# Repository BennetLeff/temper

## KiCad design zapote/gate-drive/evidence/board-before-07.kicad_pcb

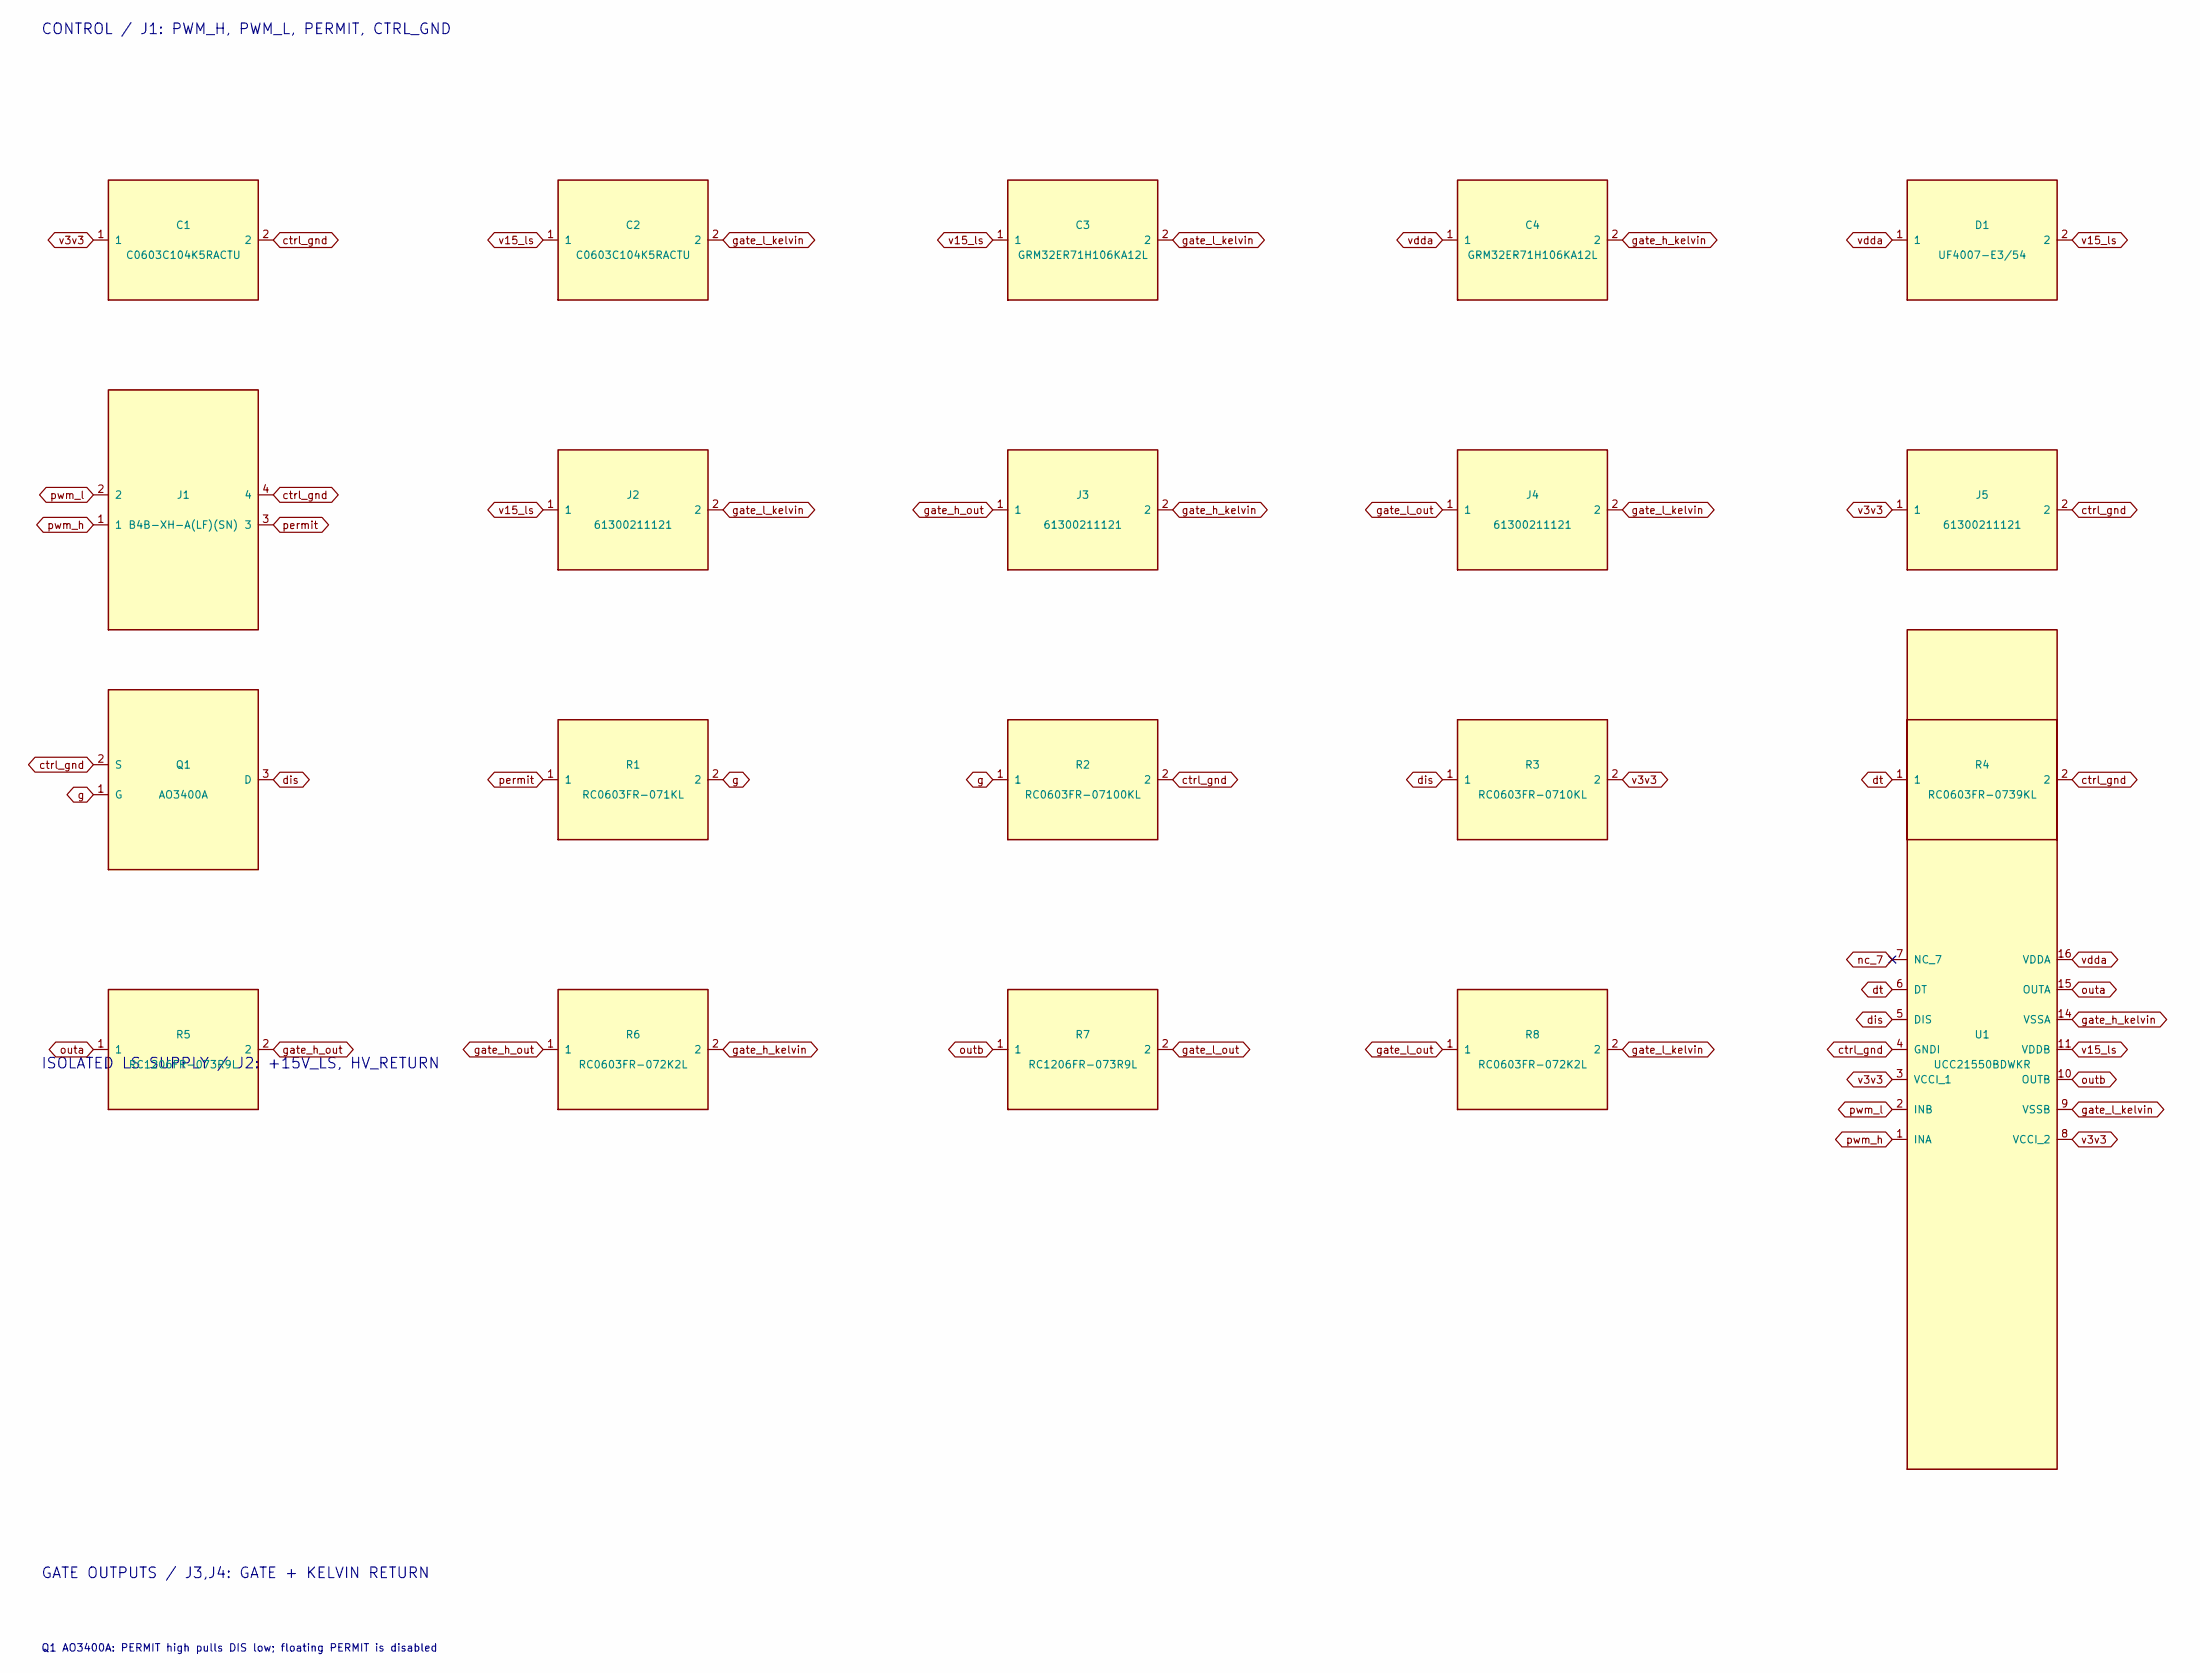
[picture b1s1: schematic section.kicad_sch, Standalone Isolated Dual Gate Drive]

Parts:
C1, C2: C0603C104K5RACTU; C_0603_1608Metric
C3, C4: GRM32ER71H106KA12L; C_1210_3225Metric
D1: UF4007-E3/54; D_DO-41_SOD81_P10.16mm_Horizontal
J1: B4B-XH-A(LF)(SN); JST_XH_B4B-XH-A_1x04_P2.50mm_Vertical
J2, J3, J4, J5: 61300211121; PinHeader_1x02_P2.54mm_Vertical
Q1: AO3400A; SOT-23
R1: RC0603FR-071KL; R_0603_1608Metric
R2: RC0603FR-07100KL; R_0603_1608Metric
R3: RC0603FR-0710KL; R_0603_1608Metric
R4: RC0603FR-0739KL; R_0603_1608Metric
R5, R7: RC1206FR-073R9L; R_1206_3216Metric
R6, R8: RC0603FR-072K2L; R_0603_1608Metric
U1: UCC21550BDWKR; SOIC16W_Isolated

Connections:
ctrl_gnd: C1.2, J1.4, J5.2, Q1.2 (S), R2.2, R4.2, U1.4 (GNDI)
dis: Q1.3 (D), R3.1, U1.5 (DIS)
dt: R4.1, U1.6 (DT)
g: Q1.1 (G), R1.2, R2.1
gate_h_kelvin: C4.2, J3.2, R6.2, U1.14 (VSSA)
gate_h_out: J3.1, R5.2, R6.1
gate_l_kelvin: C2.2, C3.2, J2.2, J4.2, R8.2, U1.9 (VSSB)
gate_l_out: J4.1, R7.2, R8.1
nc_7: U1.7 (NC_7)
outa: R5.1, U1.15 (OUTA)
outb: R7.1, U1.10 (OUTB)
permit: J1.3, R1.1
pwm_h: J1.1, U1.1 (INA)
pwm_l: J1.2, U1.2 (INB)
v3v3: C1.1, J5.1, R3.2, U1.3 (VCCI_1), U1.8 (VCCI_2)
v15_ls: C2.1, C3.1, D1.2, J2.1, U1.11 (VDDB)
vdda: C4.1, D1.1, U1.16 (VDDA)

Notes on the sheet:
CONTROL / J1: PWM_H, PWM_L, PERMIT, CTRL_GND
ISOLATED LS SUPPLY / J2: +15V_LS, HV_RETURN
GATE OUTPUTS / J3,J4: GATE + KELVIN RETURN
Q1 AO3400A: PERMIT high pulls DIS low; floating PERMIT is disabled

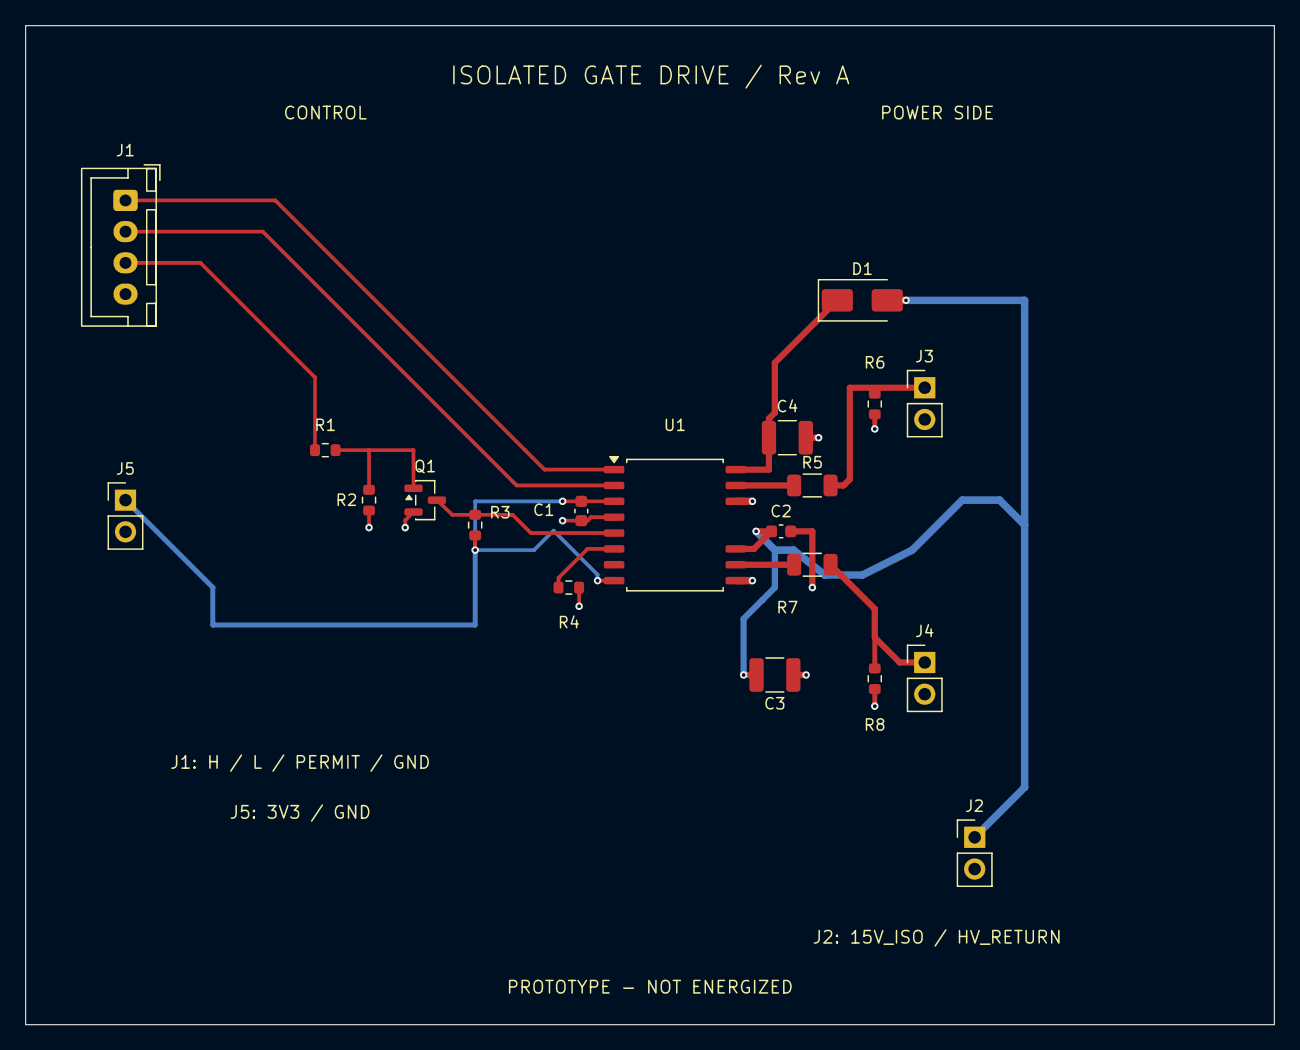
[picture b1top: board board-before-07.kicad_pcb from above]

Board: 2 copper layers, 100.0 x 80.0 mm, 20 parts (0 on the bottom side), 16 nets.

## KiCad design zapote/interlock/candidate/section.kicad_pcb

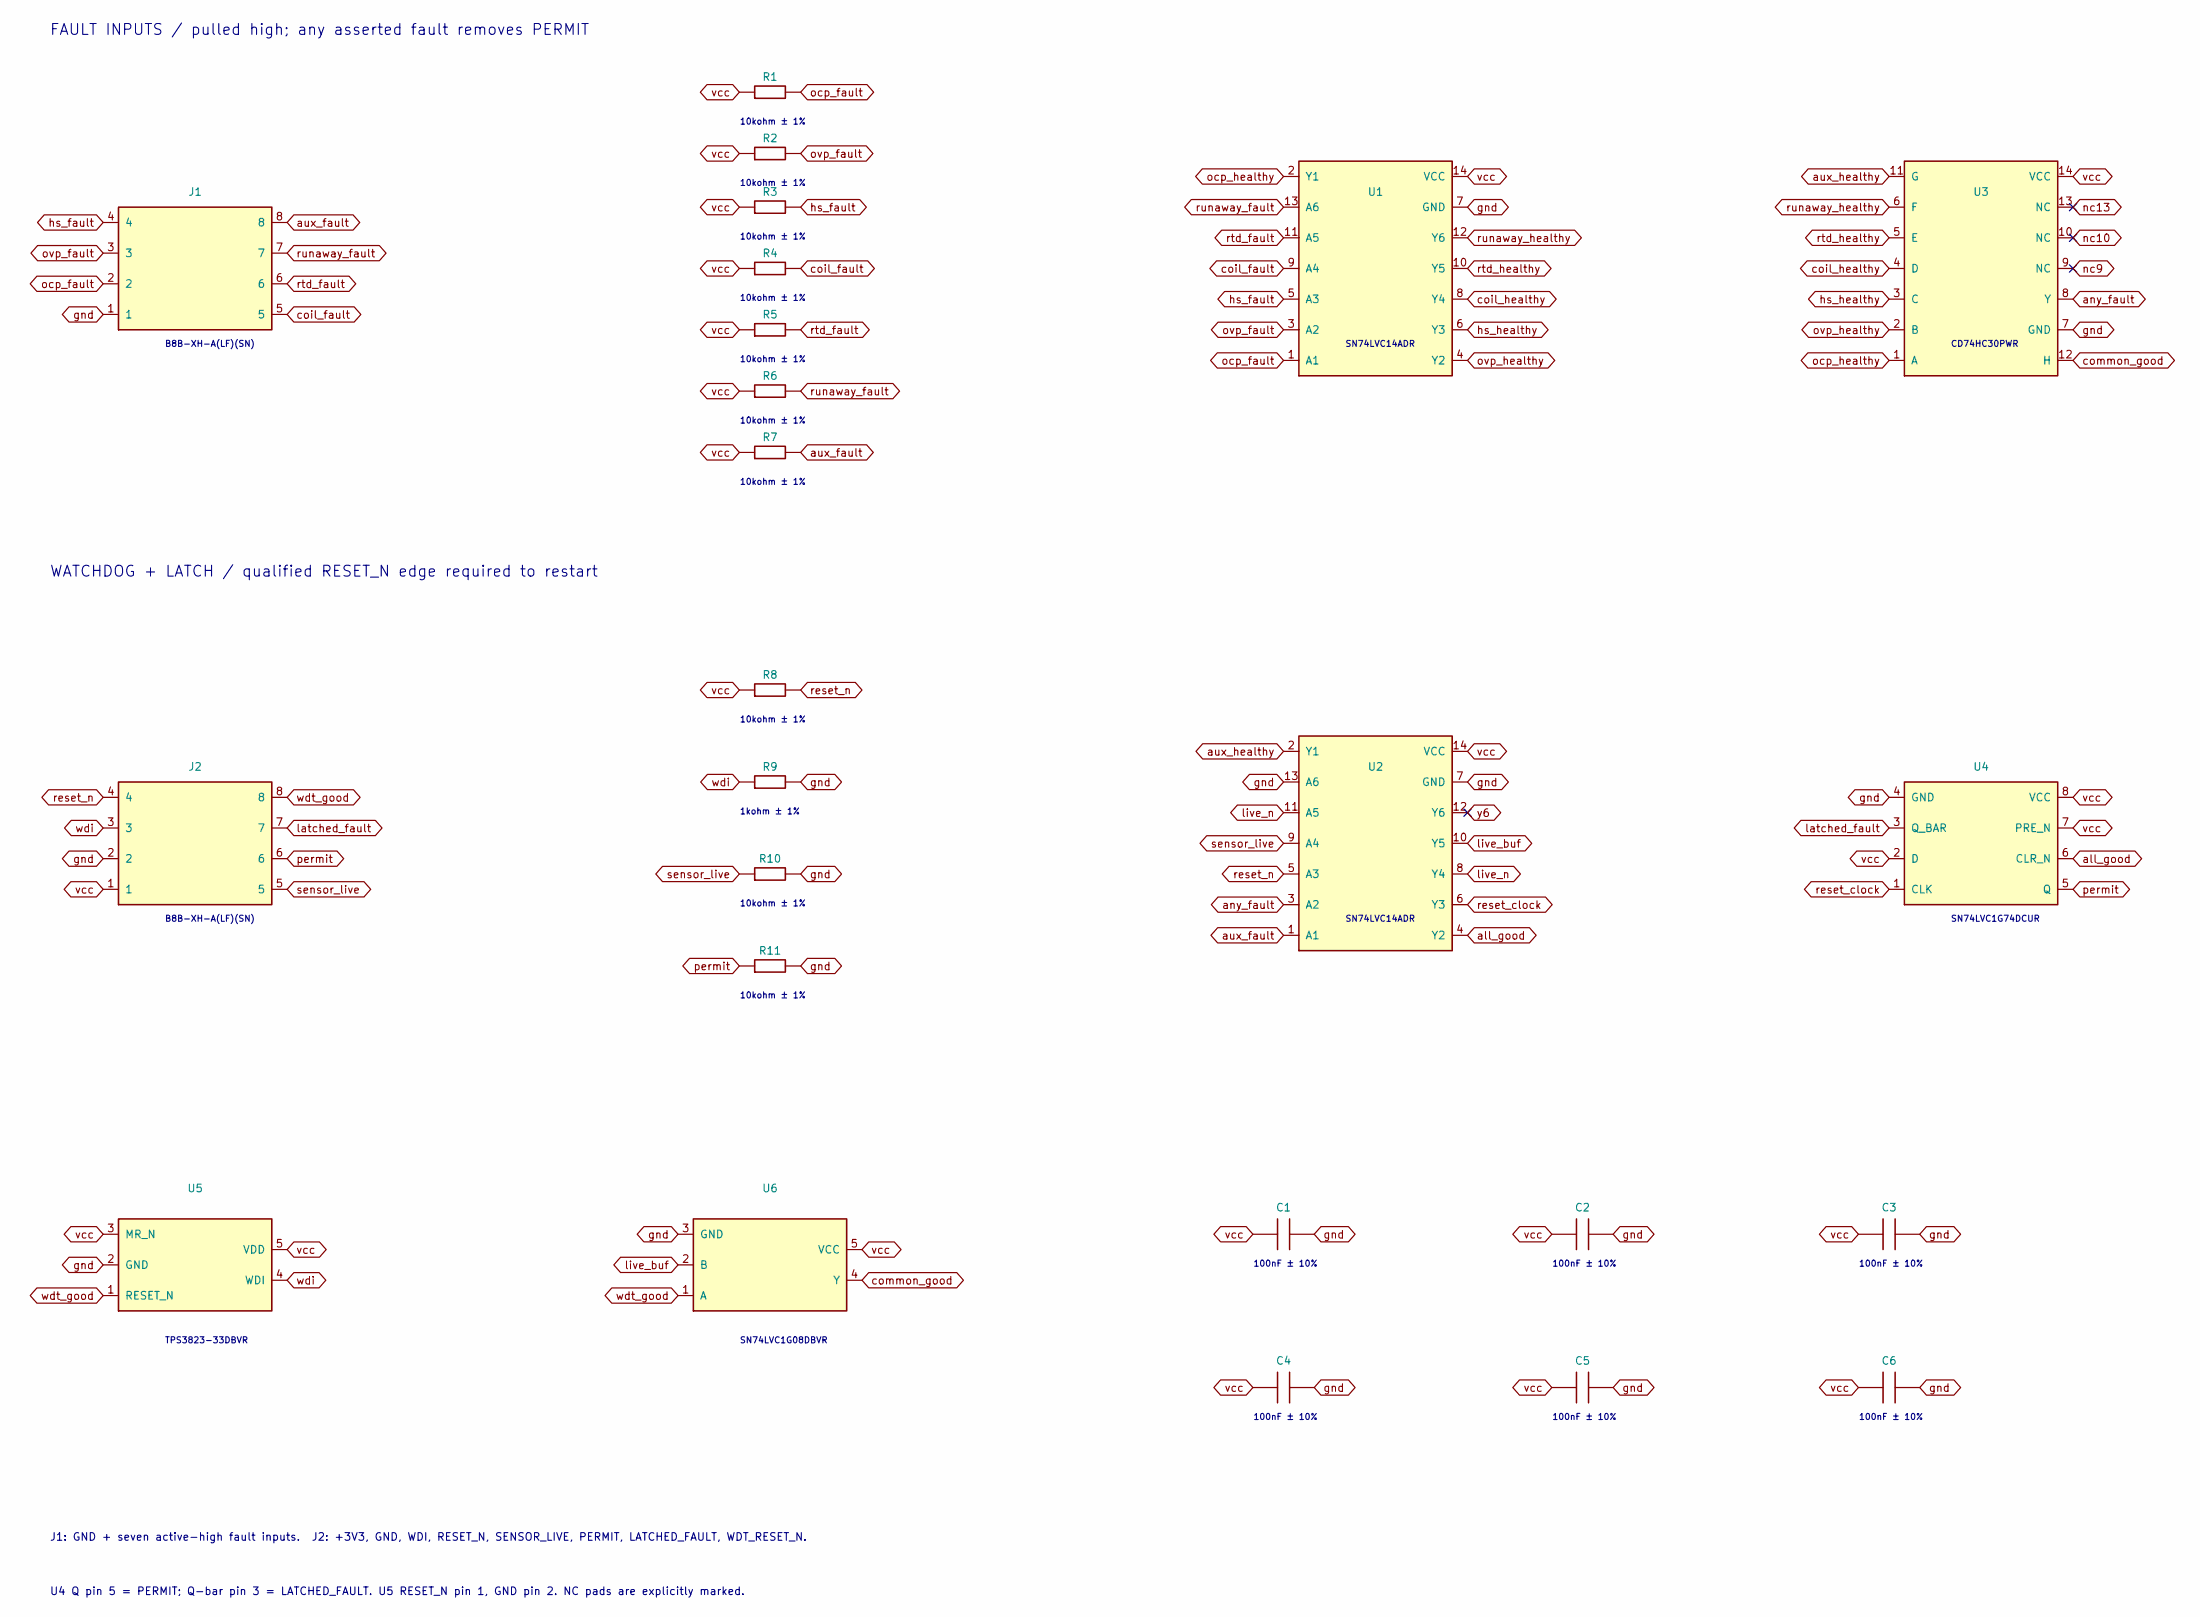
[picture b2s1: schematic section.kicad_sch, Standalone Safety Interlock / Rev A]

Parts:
C1, C2, C3, C4, C5, C6: C0603C104K5RACTU; C_0603_1608Metric
J1, J2: B8B-XH-A(LF)(SN); JST_XH_B8B-XH-A_1x08_P2.50mm_Vertical
R1, R2, R3, R4, R5, R6, R7, R8, R10, R11: RC0603FR-0710KL; R_0603_1608Metric
R9: RC0603FR-071KL; R_0603_1608Metric
U1, U2: SN74LVC14ADR; SOIC-14_3.9x8.7mm_P1.27mm
U3: CD74HC30PWR; TSSOP-14_4.4x5mm_P0.65mm
U4: SN74LVC1G74DCUR; VSSOP-8_2.3x2mm_P0.5mm
U5: TPS3823-33DBVR; SOT-23-5
U6: SN74LVC1G08DBVR; SOT-23-5

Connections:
all_good: U2.4 (Y2), U4.6 (CLR_N)
any_fault: U2.3 (A2), U3.8 (Y)
aux_fault: J1.8, R7.2, U2.1 (A1)
aux_healthy: U2.2 (Y1), U3.11 (G)
coil_fault: J1.5, R4.2, U1.9 (A4)
coil_healthy: U1.8 (Y4), U3.4 (D)
common_good: U3.12 (H), U6.4 (Y)
gnd: C1.2, C2.2, C3.2, C4.2, C5.2, C6.2, J1.1, J2.2, R9.2, R10.2, R11.2, U1.7 (GND), U2.7 (GND), U2.13 (A6), U3.7 (GND), U4.4 (GND), U5.2 (GND), U6.3 (GND)
hs_fault: J1.4, R3.2, U1.5 (A3)
hs_healthy: U1.6 (Y3), U3.3 (C)
latched_fault: J2.7, U4.3 (Q_BAR)
live_buf: U2.10 (Y5), U6.2 (B)
live_n: U2.8 (Y4), U2.11 (A5)
nc9: U3.9 (NC)
nc10: U3.10 (NC)
nc13: U3.13 (NC)
ocp_fault: J1.2, R1.2, U1.1 (A1)
ocp_healthy: U1.2 (Y1), U3.1 (A)
ovp_fault: J1.3, R2.2, U1.3 (A2)
ovp_healthy: U1.4 (Y2), U3.2 (B)
permit: J2.6, R11.1, U4.5 (Q)
reset_clock: U2.6 (Y3), U4.1 (CLK)
reset_n: J2.4, R8.2, U2.5 (A3)
rtd_fault: J1.6, R5.2, U1.11 (A5)
rtd_healthy: U1.10 (Y5), U3.5 (E)
runaway_fault: J1.7, R6.2, U1.13 (A6)
runaway_healthy: U1.12 (Y6), U3.6 (F)
sensor_live: J2.5, R10.1, U2.9 (A4)
vcc: C1.1, C2.1, C3.1, C4.1, C5.1, C6.1, J2.1, R1.1, R2.1, R3.1, R4.1, R5.1, R6.1, R7.1, R8.1, U1.14 (VCC), U2.14 (VCC), U3.14 (VCC), U4.2 (D), U4.7 (PRE_N), U4.8 (VCC), U5.3 (MR_N), U5.5 (VDD), U6.5 (VCC)
wdi: J2.3, R9.1, U5.4 (WDI)
wdt_good: J2.8, U5.1 (RESET_N), U6.1 (A)
y6: U2.12 (Y6)

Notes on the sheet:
FAULT INPUTS / pulled high; any asserted fault removes PERMIT
WATCHDOG + LATCH / qualified RESET_N edge required to restart
J1: GND + seven active-high fault inputs. J2: +3V3, GND, WDI, RESET_N, SENSOR_LIVE, PERMIT, LATCHED_FAULT, WDT_RESET_N.
U4 Q pin 5 = PERMIT; Q-bar pin 3 = LATCHED_FAULT. U5 RESET_N pin 1, GND pin 2. NC pads are explicitly marked.
100nF ± 10%
B8B-XH-A(LF)(SN)
10kohm ± 1%
1kohm ± 1%
SN74LVC14ADR
CD74HC30PWR
SN74LVC1G74DCUR
TPS3823-33DBVR
SN74LVC1G08DBVR

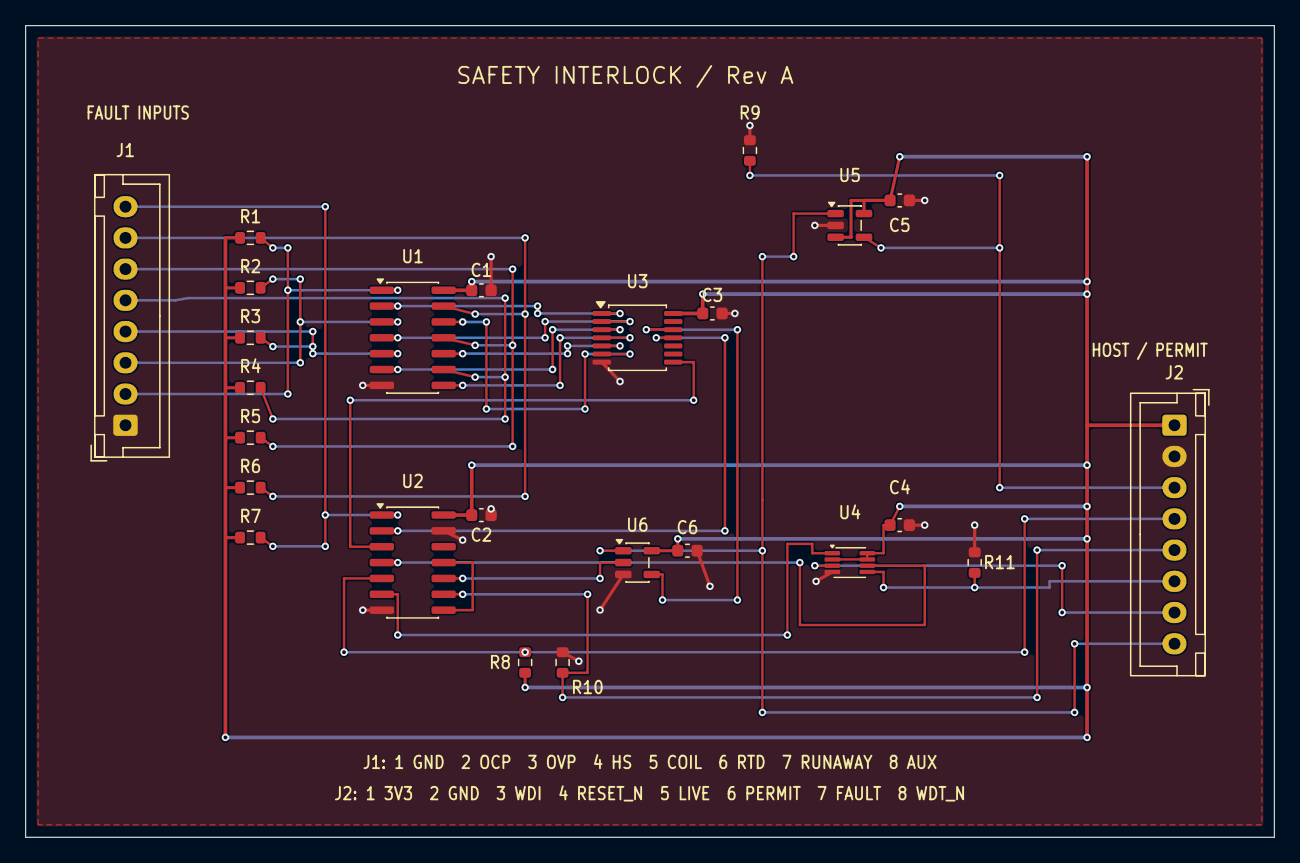
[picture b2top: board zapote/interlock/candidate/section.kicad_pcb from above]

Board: 2 copper layers, 100.0 x 65.0 mm, 25 parts (0 on the bottom side), 28 nets.
